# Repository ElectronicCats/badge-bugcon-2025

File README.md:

# Badge BugCon 2025

El Badge BugCon 2025 es un dispositivo de hardware abierto diseñado para la comunidad de hackers, desarrolladores y entusiastas de la tecnología. Cuenta con un potente procesador Linux capaz de ejecutar aplicaciones personalizadas, junto con una amplia variedad de interfaces para ampliar su funcionalidad.

## 🚀 Características Principales

### Procesador principal 
- **RV1106**: Procesador Linux de alto rendimiento
  - ARM Cortex-A7 + MCU RISC-V
  - NPU integrada (Unidad de Procesamiento Neural)
  - ISP integrado (Procesador de Señal de Imagen)
  - Soporte completo para sistemas operativos Linux

### Interfaces y Conectividad
- **GPIOs**: Múltiples pines de propósito general
- **MIPI CSI**: Interfaz para cámaras y sensores de imagen
- **UART**: Comunicación serial asíncrona
- **SPI**: Comunicación periférica de alta velocidad
- **I2C**: Bus de comunicación para sensores y pantallas
- **USB**: Puerto USB con hub integrado
- **Ethernet**: Puerto Ethernet basado en GPIO para conectividad por cable

### Periféricos Integrados
- **Neopixels**: LEDs RGB programables WS2812E
- **Batería**: Soporte para baterías 18650 con gestión de energía
- **Buck Converter**: Regulación eficiente DC-DC
- **USB-A**: Soporte para dispositivos externos

## 📦 Componentes del Proyecto

El proyecto está dividido en dos directorios principales:

### 1. Badge Principal (`Badge_Bugcon_2025/`)
Incluye el diseño principal:
- Procesador RV1106G3
- LEDs Neopixel WS2812E
- Gestión de energía y batería
- Interfaces USB

### 2. Add-on (`Add_On_Bugcon_2025/`)
Placa de expansión que incluye:
- Microcontrolador PY32F002AA15M
- Componentes adicionales para capacidades extendidas
- Diseño decorativo personalizado

## 📋 Especificaciones Técnicas

| Componente | Especificación |
|------------|----------------|
| Procesador | RV1106G3 (ARM Cortex-A7 + RISC-V MCU + NPU + ISP) |
| Sistema Operativo | Linux |
| LEDs | WS2812E Neopixels |
| Batería | Soporte 18650 |
| Interfaces | USB, Ethernet, UART, SPI, I2C, MIPI CSI, GPIOs |

## 🔌 Interfaces del RV1106

El procesador RV1106 ofrece las siguientes interfaces:

### Comunicación
- **UART**: Comunicación serial (debug/terminal)
- **SPI**: Interfaz periférica de alta velocidad
- **I2C**: Para sensores, pantallas y otros dispositivos I2C
- **USB**: Hub USB integrado

### Red
- **Ethernet**: Conectividad por cable mediante una interfaz basada en GPIO
- **WiFi (NO INCLUIDO)**: Conectividad por USB mediante el USB HUB, drivers disponibles ya instalados en kernel.

### Multimedia e Imagen
- **MIPI CSI**: Interfaz para cámaras y sensores de imagen
- **ISP**: Procesador de señal de imagen integrado

### Control
- **GPIOs**: Pines de propósito general
- **PWM**: Canales PWM para control de LEDs y motores

# Primeros pasos 

El badge Bugcon 2025 está basado en el hardware y el SDK del Luckfox Pico Pro Max. Para información general, consulta la Wiki oficial de Luckfox. El badge incorpora el RV1106G3, un microprocesador de bajo consumo de Rockchip, basado en una CPU ARM y un co-procesador RISC-V de 32 bits optimizada para aplicaciones de codificación y decodificación de audio y video.

Nuestro primer badge con Linux embebido!

El badge es compatible con múltiples interfaces, incluyendo GPIO, UART, SPI, I²C, USB, entre otras, lo que facilita un desarrollo rápido y una depuración eficiente.

## 🔌 Conectarse al puerto serial (Debug Serial)

Para interactuar con el badge (ejecutar comandos, ver logs o depurar), debes conectarte al puerto DEBUG SERIAL mostrado en la imagen anterior.
Este puerto corresponde a la UART2 del RV1106:

```
TX → GPIO1_B2_d
RX → GPIO1_B3_u
```
⚠ Importante: La señal del puerto serial del badge es 3.3V TTL.

## ✔ Adaptadores USB–Serial compatibles

Puedes usar cualquier adaptador USB a UART de 3.3V, por ejemplo:

CH340 / CH341
CP2102 / CP2104
FT232RL
PL2303
CP2105

Matek F405 adapters (soportan 3.3V)

Asegúrate de:
```
TX del adaptador → RX del badge
RX del adaptador → TX del badge
GND → GND
```

## 💻 Cómo abrir la terminal serial

A continuación, cómo conectarte desde Linux, macOS y Windows.

## 🐧 Linux

Conecta el adaptador USB-serial.

Verifica qué puerto creó:
```
dmesg | grep tty
```

Normalmente aparecerá como:
```
/dev/ttyUSB0
/dev/ttyACM0
```
Conéctate con screen o minicom:

Con screen (lo más fácil)
```
screen /dev/ttyUSB0 115200
```

Para salir:
CTRL + A luego K (y confirma).

Con minicom
```
sudo minicom -b 115200 -D /dev/ttyUSB0
```

## 🍎 macOS

Conecta el adaptador USB-UART.

Ver puertos disponibles:
```
ls /dev/tty.*
```

Suelen ser:
```
/dev/tty.usbserial-*
/dev/tty.wchusbserial*
/dev/tty.SLAB_USBtoUART
```

Conéctate:

```
screen /dev/tty.usbserial-XXXX 115200
```

Para salir:
CTRL + A, luego K.

Mac también permite usar CoolTerm (GUI amigable).

## 🪟 Windows

Usa un cliente serial como:
```
PuTTY
TeraTerm
CoolTerm
RealTerm
```

Conecta el adaptador USB-UART.

Abre el Administrador de dispositivos → “Puertos (COM y LPT)”

Identifica el puerto COM, ejemplo: COM4

Abre PuTTY o TeraTerm y selecciona:
```
Port: COM4
Baudrate: 115200
Data bits: 8
Parity: None
Stop bits: 1
Flow control: None
```
Con eso verás la consola del badge.

## Pinout 

Los números de pines correspondientes a los GPIO se encuentran marcados en el diagrama de pinout. Puedes utilizarlos para configurar un pin como GPIO.
Para más información, consulta la wiki de GPIO de Luckfox.e.

Los números de pines correspondientes a los GPIO se encuentran marcados en el diagrama de pinout. Puedes utilizarlos para configurar un pin como GPIO.
Para más información, consulta la wiki de GPIO de Luckfox.

- [GPIO](https://wiki.luckfox.com/Luckfox-Pico-Pro-Max/GPIO)

La tarjeta también es compatible con Ethernet de 10/100 Mbps. Ten en cuenta que es necesario agregar el transformador Ethernet (Ethernet transformer) y el common-mode choke para garantizar el funcionamiento adecuado del dispositivo.

Finalmente, la tarjeta permite conectar micrófonos analógicos externos a través de la entrada del códec. El CPU también puede generar señales de audio digital PCM (Pulse-Code Modulation), las cuales pueden convertirse en señales analógicas para reproducción.
Es importante destacar que la señal analógica utilizada para reproducción requiere su propio amplificador para evitar problemas relacionados con la corriente.

Para más información, consulta la wiki de audio de Luckfox:

- [Audio](https://wiki.luckfox.com/Luckfox-Pico-Ultra/Audio)

IMPORTANTE: No utilices los pines FSPI. Estos están conectados directamente a la memoria flash. Cualquier alteración en sus señales puede provocar fallos en el funcionamiento del badge.

## Blink Blink!
Presiona los botones que se encuentran al frente del badge y enciende los leds!!

## Acceso:

Para acceder al dispositivo los accesos son:

*usuario:* root

*password:* 1337

## Hola Mundo

El badge ya incluye Python 3.11.6, por lo que puedes ejecutar scripts de Python directamente desde la terminal sin necesidad de configurar nada adicional.

Esta breve guía muestra cómo crear y ejecutar un simple programa “Hola Mundo”.

1. En la terminal, crea un nuevo archivo:

```
nano nombre.py
```
o
```
vi nombre.py
```

Agrega esta linea:
```
print("Hola mundo!")
```
2. Ejecuta el archivo

```
python3 nombre.py
```

you should see
```
Hola mundo !
``` 

## NEOPIXELES

Los LEDs RGB WS2812B y WS2812E-1313 pueden controlarse utilizando el módulo de Python spidev a través de la interfaz SPI del RV1106.
Es importante destacar que SPI se utiliza como un generador de trenes de pulsos a 800 kHz, lo cual es necesario para el funcionamiento correcto de los NeoPixel.

Una vez habilitados los módulos en la interfaz de configuración y grabada la tarjeta, el siguiente paso será crear un script de Python en el entorno de Buildroot dentro de la PCB.
```
nano /root/[nombre del scrip].py
```
Puede ser algo como esto:

```
#!/usr/bin/env python3
import spidev, time, threading

SPI_SPEED_HZ = 2400000
NUM_LEDS = 8

def byte_to_spi(byte):
    spi_bytes = []
    for i in range(8):
        if byte & (1 << (7-i)):
            spi_bytes.append(0b1110)  # '1'
        else:
            spi_bytes.append(0b1000)  # '0'
    return spi_bytes

def color_to_spi(r, g, b):
    data = []
    data += byte_to_spi(g)
    data += byte_to_spi(r)
    data += byte_to_spi(b)
    return data

def make_buffer(r, g, b):
    buf = []
    for _ in range(NUM_LEDS):
        buf += color_to_spi(r, g, b)
    return buf

def run_spi(bus, device, colors):
    spi = spidev.SpiDev()
    spi.open(bus, device)
    spi.max_speed_hz = SPI_SPEED_HZ

    try:
        while True:
            for (r,g,b) in colors:
                buffer = make_buffer(r,g,b)
                spi.xfer2(buffer)
                time.sleep(1)
    except KeyboardInterrupt:
        spi.xfer2(make_buffer(0,0,0))
        spi.close()

def main():
    colors = [(255,0,255), (0,255,0), (0,0,255)]  # rosa, verde, azul

    t0 = threading.Thread(target=run_spi, args=(0,0,colors))
    #t1 = threading.Thread(target=run_spi, args=(1,0,colors))

    t0.start()
    #t1.start()

    t0.join()
    #t1.join()

if __name__ == "__main__":
    main()

```
El script controla tanto los LEDs WS2812B como WS2812B-1313 a través de spi0 y spi1, alternando entre cuatro colores diferentes (azul, rojo, verde y rosa) cada segundo.
Una vez creado, ejecuta el script:
```
python3 /root/[nombre del scrip].py
```

## Device tree source 

El Device Tree es utilizado en el kernel de Linux para describir el hardware de una placa.
Está compuesto por archivos de texto con extensiones .dts (Device Tree Source) y .dtsi (Device Tree Source Include).
El archivo .dts define el hardware específico de la placa, mientras que el archivo .dtsi contiene configuraciones comunes o compartidas por múltiples .dts.

Puedes utilizar el Device Tree para habilitar, deshabilitar y/o configurar los diferentes periféricos que la tarjeta ofrece.
Los archivos del Device Tree se encuentran en el siguiente directorio del SDK:

```
 luckfox-pico SDK/sysdrv/source/kernel/arch/arm/boot/dts
```
Para más información, consulta la wiki de DTS de Luckfox:

- [DTS](https://wiki.luckfox.com/Luckfox-Pico-Ultra/Device-Tree)

## USB host mode 

Puede modificar la configuración del device tree para establecerlo como un USB HOST, lo que le permitirá ampliar múltiples interfaces mediante un USB HUB.

1. Abre la herramienta de luckfox-config en la terminal de la badge:

```
luckfox-config
```

2. Selecciona "Advanced Options":

3. Selecciona "USB" :

4. Selecciona el modo "HOST": 

5. Una vez seleccionado, usar la tecla "Esc" para salir.

# Cargar la imagen 

## Windows

Para cargar la imagen a traves de windows, es necesario descargar este zip:
```
https://drive.google.com/drive/folders/1J3xfAAmFQHFgw1gC7Ql5-bSOi6YOyE-3
```

La carpeta contiene varias imagenes necesarias para el flasheo de la placa Bugcon2025.
Una vez descargada, por favor seguir las intrucciones de la wiki de luckfox:
```
https://wiki.luckfox.com/Luckfox-Pico-Pro-Max/Flash-image
```

## Linux

1. [Descargar](https://wiki.luckfox.com/assets/files/upgrade_tool_v2.17-bfd48dcdba9fd8013872ca2abff19a8d.zip) y extraer la herramiente de actualizacion de Rockchip.
   
3. Del release, descargar y descomprimir el archivo comprimido Bugcon-Badge-2025-vX.X.tar.xz. 
    
4. Mantenga presionado el botón BOOT mientras conecta la placa a la computadora anfitriona para entrar en modo de flasheo.

5. Una vez que tengas la placa en modo BOOT, procede a flashearla. Para ello, tendras que usar el .img que se encuentra en el archivo previamente descomprimido (modifique la ruta según la ubicación real de la imagen):

```
sudo ./upgrade_tool uf  {PATH-TO-IMAGE}/Bugcon-Badge-2025-v1.0.img
```

## MAC OS

1. [Descargar](https://wiki.luckfox.com/files/RV1106/upgrade_tool_v2.44_for_mac.zip) y extraer la herramienta de actualizacion

2. Del release, descargar y descomprimir el archivo comprimido Bugcon-Badge-2025-v1.0.tar.xz. 
    
3. Mantenga presionado el botón BOOT mientras conecta la placa a la computadora anfitriona para entrar en modo de flasheo.

4. Una vez que tengas la placa en modo BOOT, procede a flashearla. Para ello, ejecute el programa para flashear el firmware (modifique la ruta según la ubicación real de la imagen) y use el .img previamente descomprimido:
```
sudo ./upgrade_tool uf  {PATH-TO-IMAGE}/Bugcon-Badge-2025-v1.0.img
```

## 📖 Documentación Adicional

- [KiCad Documentation](https://docs.kicad.org/)
- [RV1106 Datasheet](https://files.luckfox.com/wiki/Luckfox-Pico/PDF/Rockchip%20RV1106%20Datasheet%20V1.7-20231218.pdf)
- [Proyecto basado en Luckfox](https://wiki.luckfox.com/Luckfox-Pico-RV1106)
- [SDK basado en Badge](https://github.com/ElectronicCats/luckfox-pico/tree/bugcon2025)

## 🤝 Contribuciones

Este es un proyecto de hardware abierto. Las contribuciones son bienvenidas:

1. Haz un fork del repositorio.
2. Crea una nueva rama para tu feature (`git checkout -b feature/AmazingFeature`)
3. Haz commit de tus cambios (`git commit -m 'Add some AmazingFeature'`)
4. Haz push a tu rama (`git push origin feature/AmazingFeature`)
5. Abre un Pull Request

## 📝 Licencia

Este proyecto es de hardware abierto. Consulta los archivos de licencia para más detalles.

## 🏢 Electronic Cats

Desarollado con ❤️ por [Electronic Cats](https://www.electroniccats.com/)

Electronic Cats invierte tiempo y recursos en proporcionar este diseño de hardware abierto.
Por favor, apoya a Electronic Cats y al hardware abierto comprando productos de Electronic Cats.

## 📞 Contacto y soporte 

- **Website**: [https://www.electroniccats.com/](https://www.electroniccats.com/)
- **GitHub**: [ElectronicCats](https://github.com/ElectronicCats)
- **Issues**: Usa la sección de Issues en GitHub para reportar problemas o sugerir mejoras

## 🙏 Agradecimientos

Gracias a toda la comunidad de hardware abierto y a todas las personas que hacen posibles proyectos como este.
---

Nota: Este badge está diseñado para BugCon 2025. Para más información sobre el evento, visita la página oficial de BugCon.

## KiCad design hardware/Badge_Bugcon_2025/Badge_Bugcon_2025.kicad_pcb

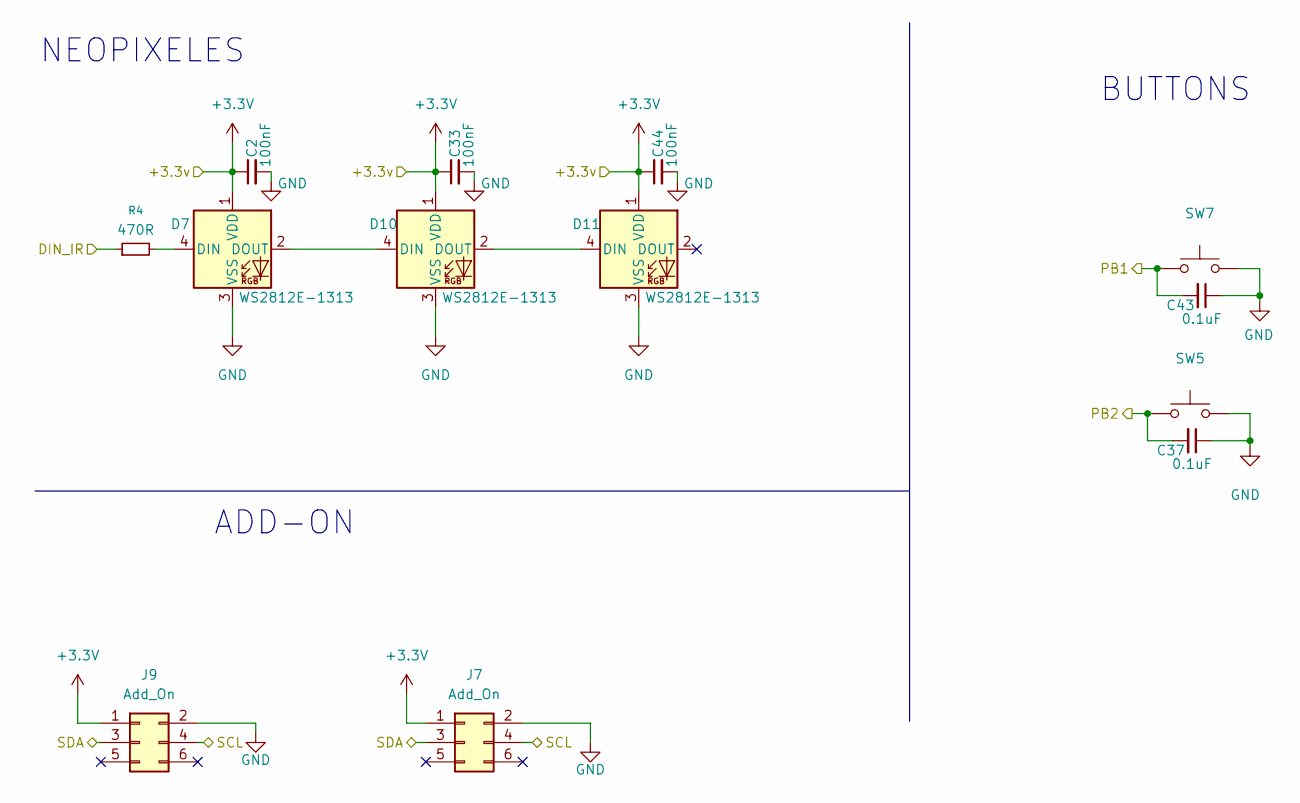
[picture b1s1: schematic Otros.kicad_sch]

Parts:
C2, C33, C44: 100nF; C_0402_1005Metric; LCSC# C77020
C37, C43: 0.1uF; C_0603_1608Metric; LCSC# C478888
D7, D10, D11: WS2812E-1313; LCSC# C5446700
J7, J9: Add_On; PinSocket_2x03_P2.54mm_Vertical; LCSC# C5116527
R4: 470R; R_0603_1608Metric; LCSC# C23179
SW5, SW7: SW_SPST_TL3342; LCSC# C318889

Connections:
+3.3V: C2.1, C33.1, C44.1, D7.1 (VDD), D10.1 (VDD), D11.1 (VDD), J7.1, J9.1; also elsewhere on the board
/MCU/DIN_IR: R4.1; also elsewhere on the board
/MCU/PB1: C43.2, SW7.2; also elsewhere on the board
/MCU/PB2: C37.2, SW5.2; also elsewhere on the board
/MCU/SCL: J7.4, J9.4; also elsewhere on the board
/MCU/SDA: J7.3, J9.3; also elsewhere on the board
GND: C2.2, C33.2, C37.1, C43.1, C44.2, D7.3 (VSS), D10.3 (VSS), D11.3 (VSS), J7.2, J9.2, SW5.1, SW7.1; also elsewhere on the board
unnamed: D7.4 (DIN), R4.2
unnamed: D7.2 (DOUT), D10.4 (DIN)
unnamed: D10.2 (DOUT), D11.4 (DIN)

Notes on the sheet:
BUTTONS
NEOPIXELES
ADD-ON

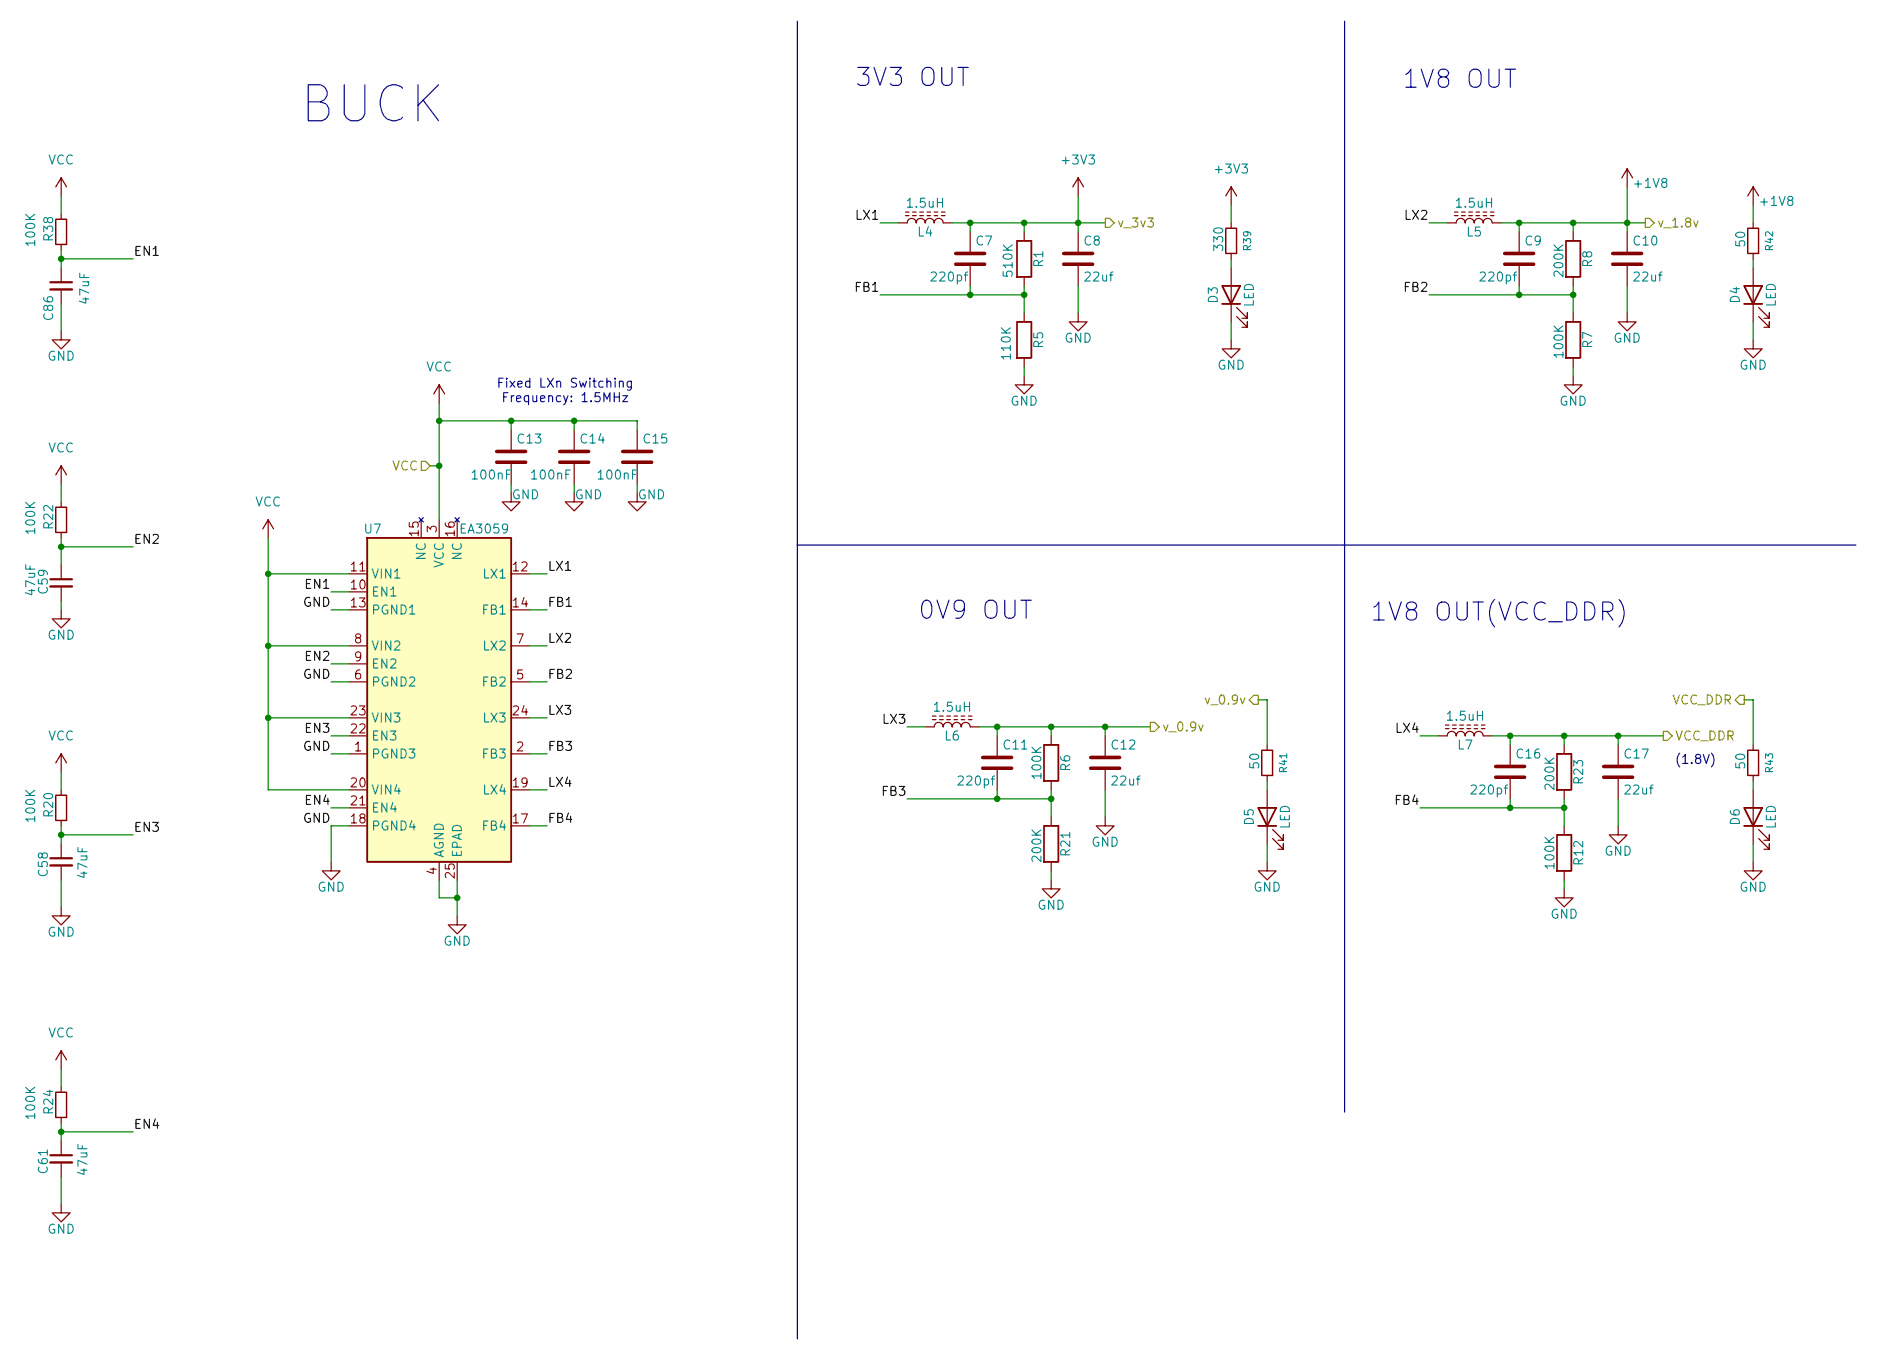
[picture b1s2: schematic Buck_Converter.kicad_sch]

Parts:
C7, C9, C11, C16: 220pf; C_0402_1005Metric; LCSC# C107001
C8, C10, C12, C17: 22uf; C_0402_1005Metric; LCSC# C415703
C13, C14, C15: 100nF; C_0402_1005Metric; LCSC# C77020
C58, C59, C61, C86: 47uF; C_0603_1608Metric; LCSC# C140782
D3, D4, D5, D6: LED; LED_0603_1608Metric; LCSC# C375573
L4, L5, L6, L7: 1.5uH; L_1008_2520Metric; LCSC# C7427193
R1: 510K; R_0402_1005Metric; LCSC# C365024
R5: 110K; R_0402_1005Metric; LCSC# C2909311
R6, R7, R12, R20, R22, R24, R38: 100K; R_0402_1005Metric; LCSC# C844674
R8, R21, R23: 200K; R_0402_1005Metric; LCSC# C364966
R39: 330; R_0402_1005Metric; LCSC# C105875
R41, R42, R43: 50; R_0603_1608Metric; LCSC# C2907181
U7: EA3059; VQFN-24-1EP_4x4mm_P0.5mm_EP2.5x2.5mm; LCSC# C111586

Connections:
+1V8: C9.1, C10.1, L5.2, R8.1, R42.2; also elsewhere on the board
+3V3: C7.1, C8.1, L4.2, R1.1, R39.2; also elsewhere on the board
/Buck_Converter/EN1: C86.1, R38.1, U7.10 (EN1)
/Buck_Converter/EN2: C59.1, R22.1, U7.9 (EN2)
/Buck_Converter/EN3: C58.1, R20.1, U7.22 (EN3)
/Buck_Converter/EN4: C61.1, R24.1, U7.21 (EN4)
/Buck_Converter/FB1: C7.2, R1.2, R5.1, U7.14 (FB1)
/Buck_Converter/FB2: C9.2, R7.1, R8.2, U7.5 (FB2)
/Buck_Converter/FB3: C11.2, R6.2, R21.1, U7.2 (FB3)
/Buck_Converter/FB4: C16.2, R12.1, R23.2, U7.17 (FB4)
/Buck_Converter/LX1: L4.1, U7.12 (LX1)
/Buck_Converter/LX2: L5.1, U7.7 (LX2)
/Buck_Converter/LX3: L6.1, U7.24 (LX3)
/Buck_Converter/LX4: L7.1, U7.19 (LX4)
/Buck_Converter/VCC_DDR: C16.1, C17.1, L7.2, R23.1, R43.2; also elsewhere on the board
/Buck_Converter/v_0.9v: C11.1, C12.1, L6.2, R6.1, R41.2; also elsewhere on the board
GND: C8.2, C10.2, C12.2, C13.2, C14.2, C15.2, C17.2, C58.2, C59.2, C61.2, C86.2, D3.1 (K), D4.1 (K), D5.1 (K), D6.1 (K), R5.2, R7.2, R12.2, R21.2, U7.1 (PGND3), U7.4 (AGND), U7.6 (PGND2), U7.13 (PGND1), U7.18 (PGND4), U7.25 (EPAD); also elsewhere on the board
unnamed: D3.2 (A), R39.1
unnamed: D4.2 (A), R42.1
unnamed: D5.2 (A), R41.1
unnamed: D6.2 (A), R43.1

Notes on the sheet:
BUCK
0V9 OUT
Fixed LXn Switching Frequency: 1.5MHz
(1.8V)
1V8 OUT(VCC_DDR)
3V3 OUT
1V8 OUT

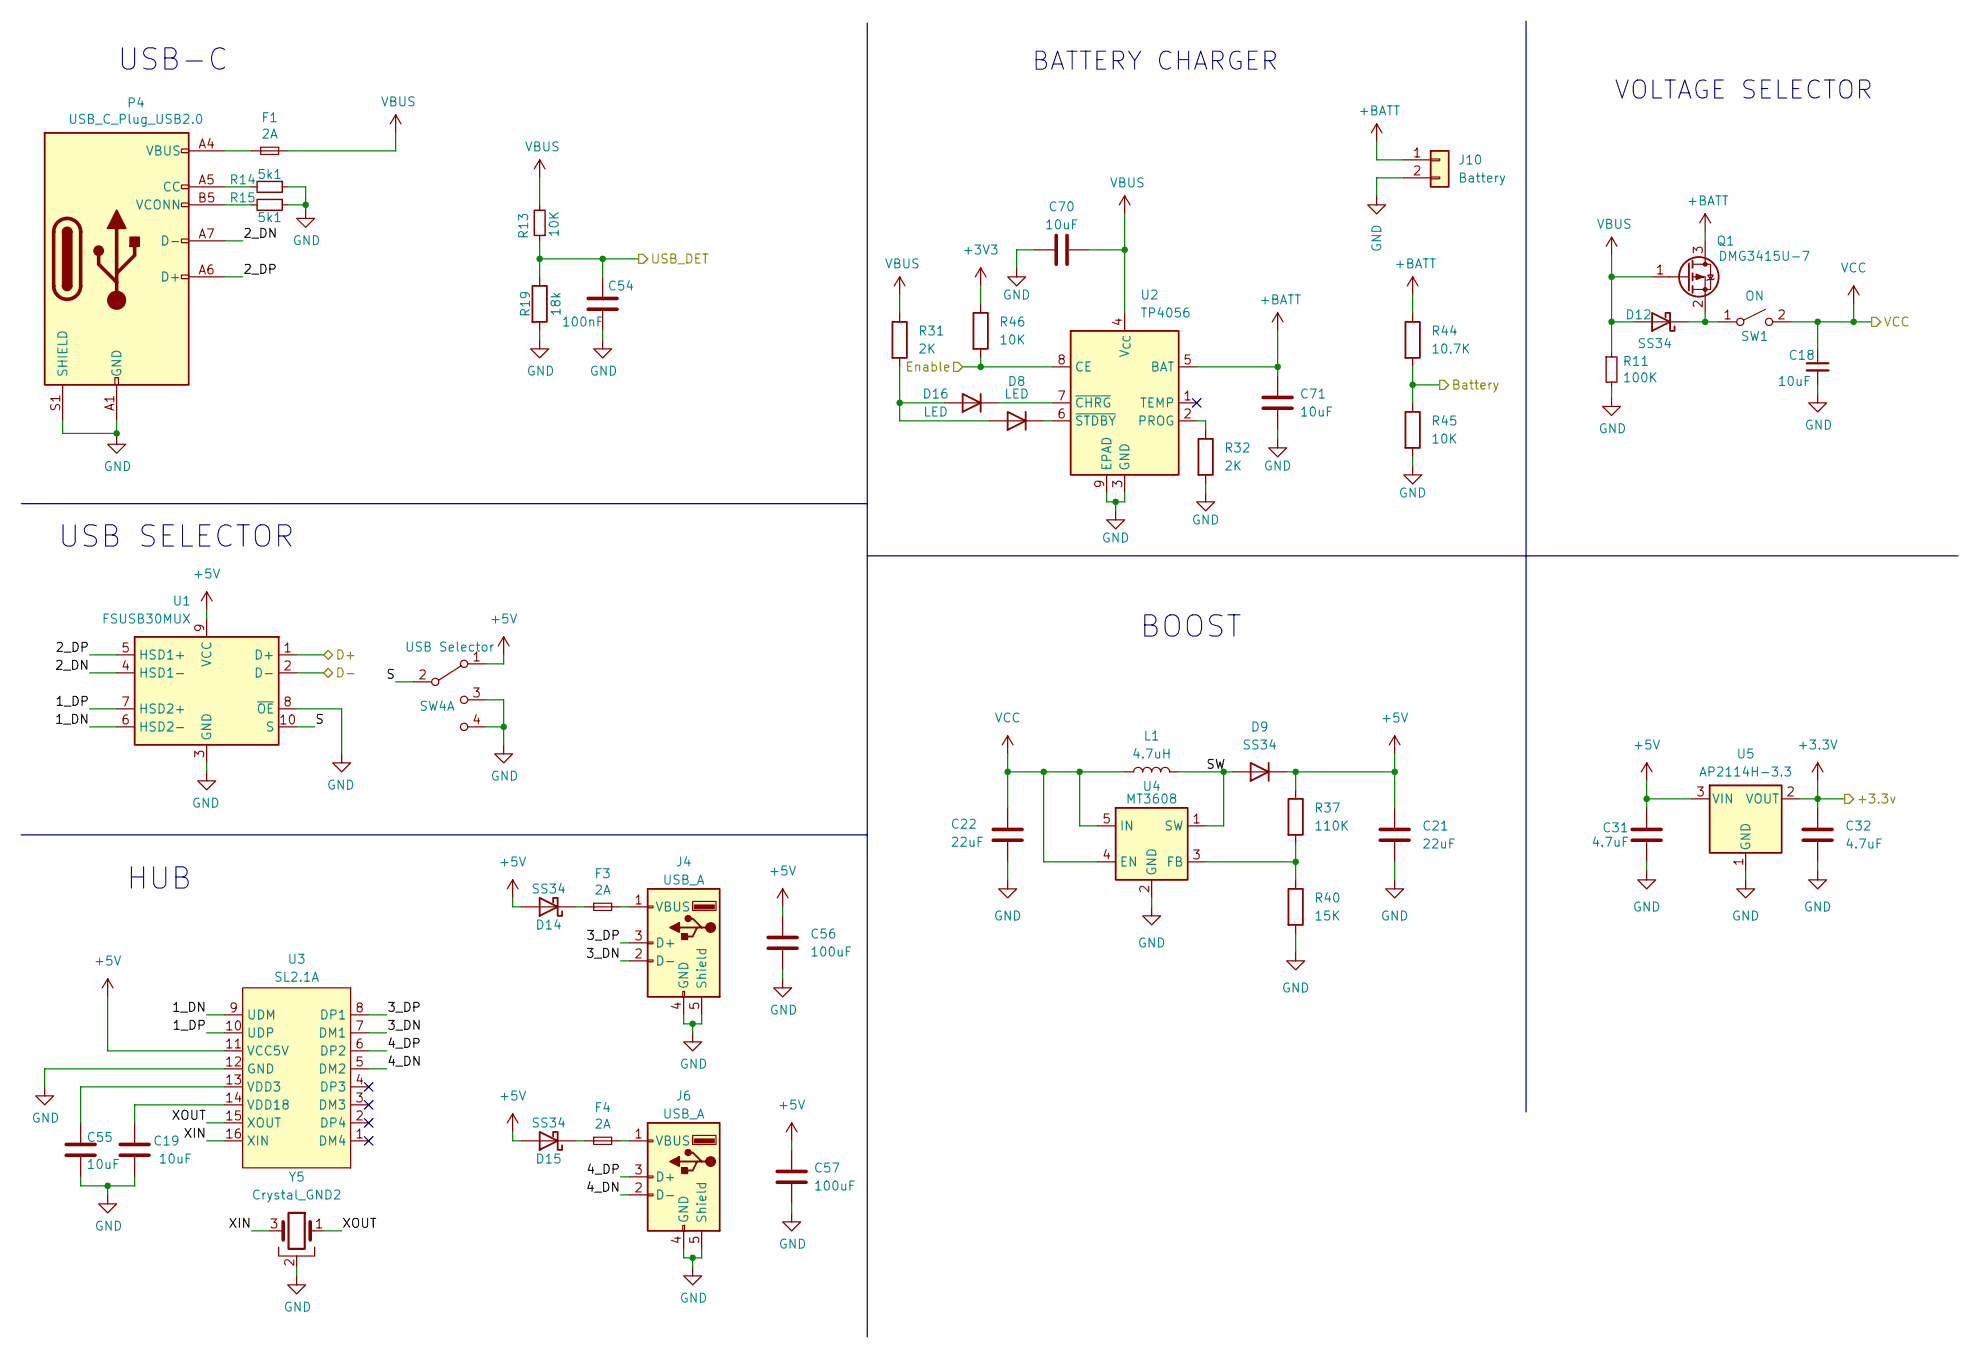
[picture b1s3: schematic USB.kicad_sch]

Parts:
C18: 10uF; C_0402_1005Metric; LCSC# C7472949
C19, C55, C70, C71: 10uF; C_0603_1608Metric; LCSC# C96446
C21, C22: 22uF; C_0402_1005Metric; LCSC# C415703
C31, C32: 4.7uF; C_0402_1005Metric; LCSC# C368809
C54: 100nF; C_0402_1005Metric; LCSC# C77020
C56, C57: 100uF; C_0805_2012Metric; LCSC# C141660
D8, D16: LED; LED_0603_1608Metric; LCSC# C375573
D9, D12, D14, D15: SS34; D_SMA; LCSC# C908680
F1, F3, F4: 2A; Fuse_0603_1608Metric; LCSC# C41380229
J4, J6: USB_A; USB_A_Connfly_DS1095; LCSC# C2345
J10: Battery; BatteryHolder_Keystone_1042_1x18650; LCSC# C2988620
L1: 4.7uH; LQH5BPN; LCSC# C520334
P4: USB_C_Plug_USB2.0; C393939; LCSC# C2760486
Q1: DMG3415U-7; SOT-23; LCSC# C96616
R11: 100K; R_0603_1608Metric; LCSC# C15458
R13, R45, R46: 10K; R_0402_1005Metric; LCSC# C2759535
R14, R15: 5k1; R_0603_1608Metric; LCSC# C2907044
R19: 18k; R_0402_1005Metric; LCSC# C323741
R31, R32: 2K; R_0603_1608Metric; LCSC# C2907022
R37: 110K; R_0603_1608Metric; LCSC# C326736
R40: 15K; R_0603_1608Metric; LCSC# C2989599
R44: 10.7K; R_0402_1005Metric; LCSC# C2998172
SW1: ON; SW_Slide_SPDT_Angled_CK_OS102011MA1Q; LCSC# C393937
SW4: USB Selector; SW_Slide_SPDT_Angled_CK_OS102011MA1Q; LCSC# C393937
U1: FSUSB30MUX; IC_FSUSB42UMX; LCSC# C42370490
U2: TP4056; SOIC-8-1EP_3.9x4.9mm_P1.27mm_EP2.41x3.3mm_ThermalVias; LCSC# C725790
U3: SL2.1A; SOP-16_3.9x9.9mm_P1.27mm; LCSC# C192893
U4: MT3608; SOT-23-6; LCSC# C2932326
U5: AP2114H-3.3; SOT-223-3_TabPin2; LCSC# C150716
Y5: Crystal_GND2; Crystal_SMD_3225-4Pin_3.2x2.5mm; LCSC# C133334

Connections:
+3.3V: C32.1, U5.2 (VOUT); also elsewhere on the board
+3V3: R46.1; also elsewhere on the board
+BATT: C71.1, J10.1, Q1.3 (D), R44.1, U2.5 (BAT)
/MCU/Battery: R44.2, R45.1; also elsewhere on the board
/MCU/D+: U1.1 (D+); also elsewhere on the board
/MCU/D-: U1.2 (D-); also elsewhere on the board
/MCU/Enable: R46.2, U2.8 (CE); also elsewhere on the board
/MCU/USB_DET: C54.1, R13.1, R19.1; also elsewhere on the board
/USB/1_DN: U1.6 (HSD2-), U3.9 (UDM)
/USB/1_DP: U1.7 (HSD2+), U3.10 (UDP)
/USB/2_DN: P4.A7 (D-), U1.4 (HSD1-)
/USB/2_DP: P4.A6 (D+), U1.5 (HSD1+)
/USB/3_DN: J4.2 (D-), U3.7 (DM1)
/USB/3_DP: J4.3 (D+), U3.8 (DP1)
/USB/4_DN: J6.2 (D-), U3.5 (DM2)
/USB/4_DP: J6.3 (D+), U3.6 (DP2)
/USB/S: SW4.2 (B), U1.10 (S)
/USB/SW: D9.2 (A), L1.2, U4.1 (SW)
/USB/XIN: U3.16 (XIN), Y5.3
/USB/XOUT: U3.15 (XOUT), Y5.1
GND: C18.2, C19.1, C21.2, C22.2, C31.2, C32.2, C54.2, C55.2, C56.2, C57.2, C70.1, C71.2, J4.4 (GND), J4.5 (Shield), J6.4 (GND), J6.5 (Shield), J10.2, P4.A1 (GND), P4.A12 (GND), P4.B1 (GND), P4.B12 (GND), P4.S1 (SHIELD), R11.2, R14.1, R15.1, R19.2, R32.2, R40.2, R45.2, SW4.3 (C), SW4.4 (C), U1.3 (GND), U1.8 (~OE), U2.3 (GND), U2.9 (EPAD), U3.12 (GND), U4.2 (GND), U5.1 (GND), Y5.2, Y5.4; also elsewhere on the board
unnamed: D8.1 (K), U2.6 (~STDBY)
unnamed: D12.1 (K), Q1.2 (S), SW1.1 (A)
unnamed: D14.1 (K), F3.1
unnamed: D15.1 (K), F4.1
unnamed: D8.2 (A), D16.2 (A), R31.2
unnamed: D16.1 (K), U2.7 (~CHRG)
unnamed: F1.1, P4.A4 (VBUS), P4.A9 (VBUS), P4.B4 (VBUS), P4.B9 (VBUS)
unnamed: F3.2, J4.1 (VBUS)
unnamed: F4.2, J6.1 (VBUS)
unnamed: P4.A5 (CC), R14.2
unnamed: P4.B5 (VCONN), R15.2
unnamed: R32.1, U2.2 (PROG)
unnamed: C55.1, U3.13 (VDD3)
unnamed: C19.2, U3.14 (VDD18)
unnamed: R37.2, R40.1, U4.3 (FB)
VBUS: C70.2, D12.2 (A), F1.2, Q1.1 (G), R11.1, R13.2, R31.1, U2.4 (V_{CC})

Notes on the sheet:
VOLTAGE SELECTOR
BOOST
USB-C
USB SELECTOR
BATTERY CHARGER
HUB
